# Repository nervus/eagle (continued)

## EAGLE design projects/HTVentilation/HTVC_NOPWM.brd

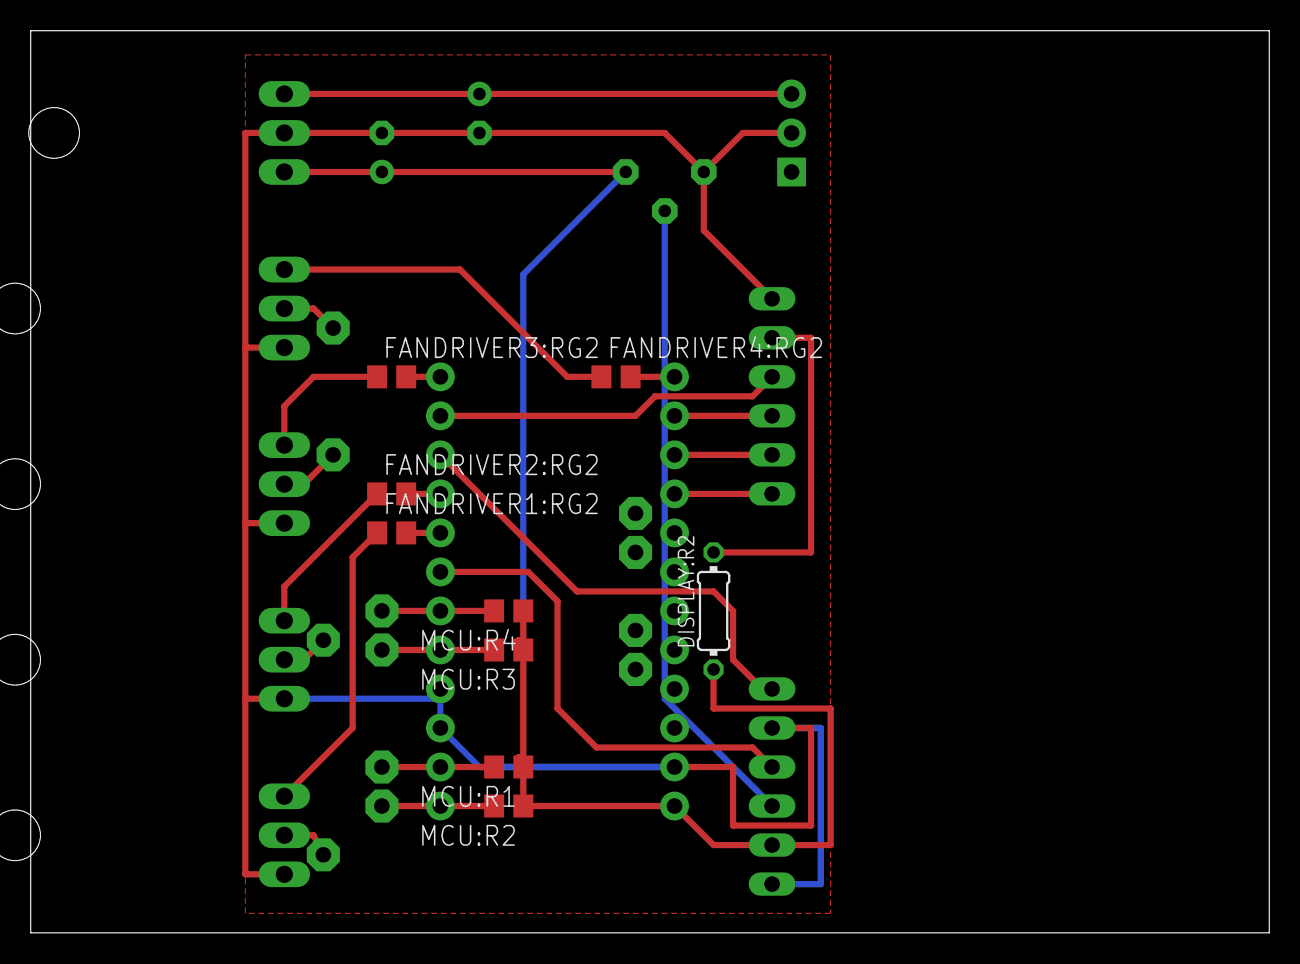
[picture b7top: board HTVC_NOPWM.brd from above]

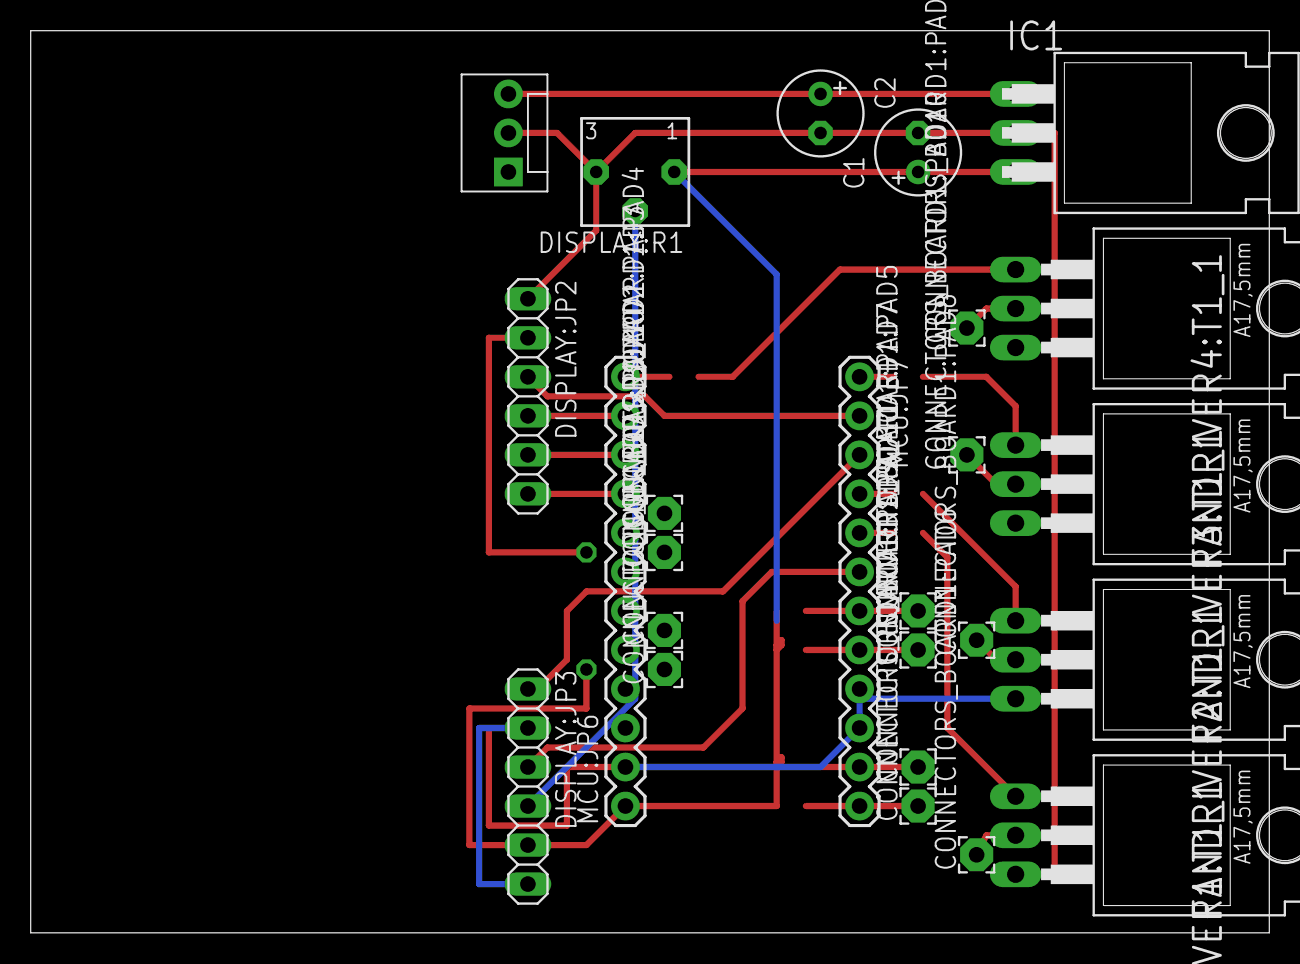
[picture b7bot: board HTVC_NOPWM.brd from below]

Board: 2 copper layers, 80.6 x 58.7 mm, 34 parts (25 on the bottom side), 31 nets.

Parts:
C1: 0.33uF; E2,5-6
C2: 0.1uF; E2,5-6
CONNECTORS_BOARD1:PAD1, CONNECTORS_BOARD1:PAD2, CONNECTORS_BOARD1:PAD3, CONNECTORS_BOARD1:PAD4, CONNECTORS_BOARD1:PAD5, CONNECTORS_BOARD1:PAD6, CONNECTORS_BOARD1:PAD7, CONNECTORS_BOARD1:PAD8, CONNECTORS_BOARD1:PAD9, CONNECTORS_BOARD1:PAD10, CONNECTORS_BOARD1:PAD11, CONNECTORS_BOARD1:PAD12: 2,15/1,0
DISPLAY:JP2, DISPLAY:JP3: 1X06
DISPLAY:R1: 10k; 3362P
DISPLAY:R2: 470R; 0204/7
FANDRIVER1:RG2, FANDRIVER2:RG2, FANDRIVER3:RG2, FANDRIVER4:RG2: 1K; R0805
FANDRIVER1:T1_1, FANDRIVER2:T1_1, FANDRIVER3:T1_1, FANDRIVER4:T1_1: TIP120; TO220AH
IC1: 7805T; TO220H
JP1: MOLEX-1X3
MCU:JP6, MCU:JP7: 1X12
MCU:R1, MCU:R2, MCU:R3, MCU:R4: 10K; R0805

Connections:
+5V: C2.+, DISPLAY:JP3.5, DISPLAY:R1.1, DISPLAY:R2.1, IC1.3, MCU:JP6.1, MCU:R1.1, MCU:R2.1, MCU:R3.1, MCU:R4.1
A0: CONNECTORS_BOARD1:PAD1.1, MCU:JP6.8
A1: CONNECTORS_BOARD1:PAD2.1, MCU:JP6.7
A2: CONNECTORS_BOARD1:PAD3.1, MCU:JP6.6
A3: CONNECTORS_BOARD1:PAD4.1, MCU:JP6.5
AGND: C1.-, C2.-, DISPLAY:JP2.1, DISPLAY:JP3.2, DISPLAY:JP3.6, DISPLAY:R1.3, FANDRIVER1:T1_1.E, FANDRIVER2:T1_1.E, FANDRIVER3:T1_1.E, FANDRIVER4:T1_1.E, IC1.2, JP1.2, MCU:JP6.2, MCU:JP7.9, MCU:JP7.10
DISPLAY:N$1: DISPLAY:JP3.4, DISPLAY:R1.2
DISPLAY:N$2: DISPLAY:JP2.2, DISPLAY:R2.2
FANDRIVER1:N$10: FANDRIVER1:RG2.1, FANDRIVER1:T1_1.B
FANDRIVER2:N$10: FANDRIVER2:RG2.1, FANDRIVER2:T1_1.B
FANDRIVER3:N$10: FANDRIVER3:RG2.1, FANDRIVER3:T1_1.B
FANDRIVER4:N$10: FANDRIVER4:RG2.1, FANDRIVER4:T1_1.B
unnamed: DISPLAY:JP3.3, MCU:JP7.6
unnamed: DISPLAY:JP3.1, MCU:JP7.3
unnamed: DISPLAY:JP2.6, MCU:JP6.9
unnamed: DISPLAY:JP2.5, MCU:JP6.10
unnamed: DISPLAY:JP2.4, MCU:JP6.11
unnamed: DISPLAY:JP2.3, MCU:JP7.2
unnamed: CONNECTORS_BOARD1:PAD12.1, FANDRIVER4:T1_1.C
unnamed: CONNECTORS_BOARD1:PAD10.1, FANDRIVER3:T1_1.C
unnamed: CONNECTORS_BOARD1:PAD8.1, FANDRIVER2:T1_1.C
unnamed: CONNECTORS_BOARD1:PAD6.1, FANDRIVER1:T1_1.C
unnamed: FANDRIVER1:RG2.2, MCU:JP7.5
unnamed: FANDRIVER2:RG2.2, MCU:JP7.4
unnamed: FANDRIVER3:RG2.2, MCU:JP7.1
unnamed: FANDRIVER4:RG2.2, MCU:JP6.12
TACH0: CONNECTORS_BOARD1:PAD5.1, MCU:JP7.7, MCU:R4.2
TACH1: CONNECTORS_BOARD1:PAD7.1, MCU:JP7.8, MCU:R3.2
TACH2: CONNECTORS_BOARD1:PAD9.1, MCU:JP7.12, MCU:R2.2
TACH3: CONNECTORS_BOARD1:PAD11.1, MCU:JP7.11, MCU:R1.2
VCC: C1.+, IC1.1, JP1.3

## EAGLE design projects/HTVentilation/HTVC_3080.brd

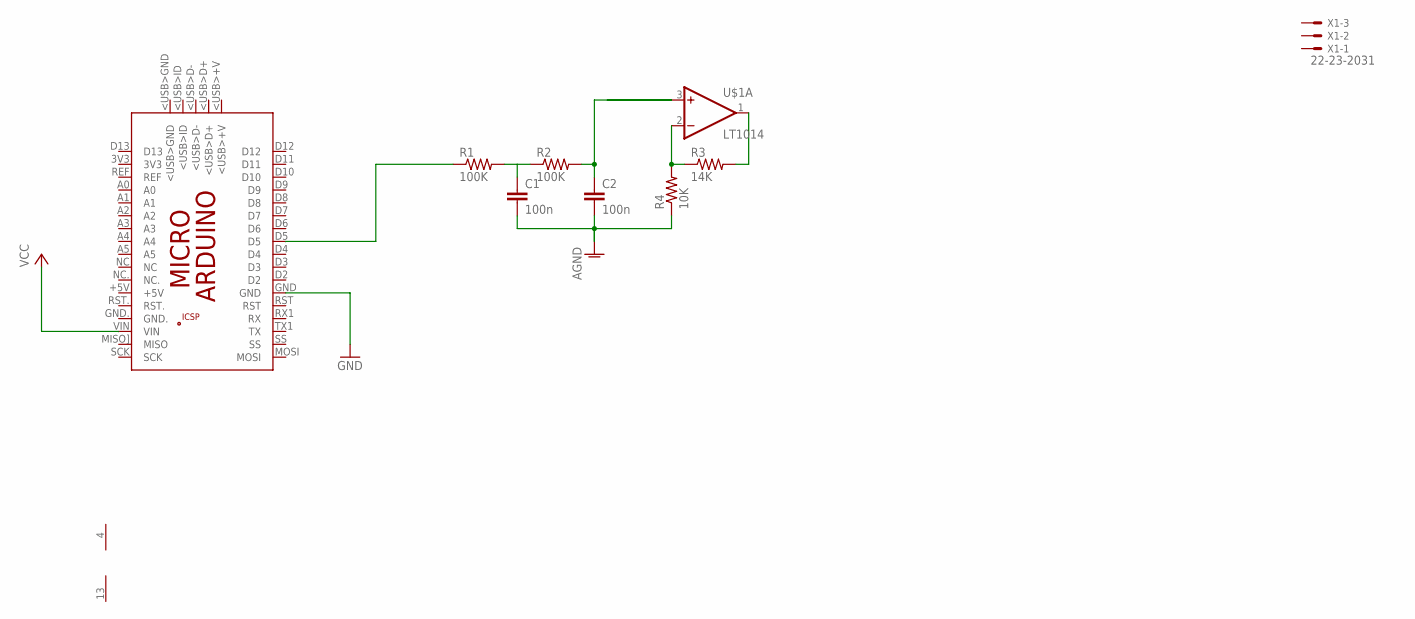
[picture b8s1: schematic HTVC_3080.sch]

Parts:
C1, C2: 100n; C0805
PCB1: ARDUINO_MICRO
R1, R2: 100K; R0805
R3: 14K; R0805
R4: 10K; R0805
U$1: LT1014; SO16
X1: 22-23-2031

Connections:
AGND: C1.2, C2.2, R4.1
GND: PCB1.GND
unnamed: PCB1.D5, R1.1
unnamed: R3.2, U$1.1 (OUT)
unnamed: C1.1, R1.2, R2.1
unnamed: C2.1, R2.2, U$1.3 (+IN)
unnamed: R3.1, R4.2, U$1.2 (-IN)
V+: U$1.4 (V+)
V-: U$1.13 (V-)
VCC: PCB1.VIN

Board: 2 copper layers, 9 parts (0 on the bottom side), 6 nets, no tracks yet.

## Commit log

2015-05-23 added things
2015-05-23 smaller traces + images
2015-05-24 replaced with the proper cap package
2015-05-24 made nice traces for the caps
2015-06-07 added TSOT23-5 package
2015-07-02 added another variant for the rcswitch
2015-09-08 added SO16, SO16L packages + LT1014 quad opamp
2015-09-08 Added TTSOP16, TTSOP16EXP and LT3083EFE
2015-09-14 added more stuff
    3362 trim
    sot223
    to92
    to220-51
    lt3080
    lm35
2015-09-19 Added a Schottky diode
    MBRS240LT3
2015-09-19 Rev1 of temperature fan controller
2015-09-19 temperature controlled fan speed controller
2015-09-19 remove old design
2015-09-19 added no smd version
    through hole non temperature controlled version
2015-10-12 new items in the lib + new 4 layer board
2015-10-12 cleanup
2015-10-12 more cleanup
2015-11-09 usb micro ab
2015-11-09 v3 as sent to fab
2015-11-09 v3 fab
2020-05-11 added AD5676RBRUZ
